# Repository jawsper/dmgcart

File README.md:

# dmgcart
DMGcart: STM32F429 based Game Boy flashcart

These are the hardware design files for the DMGcart.

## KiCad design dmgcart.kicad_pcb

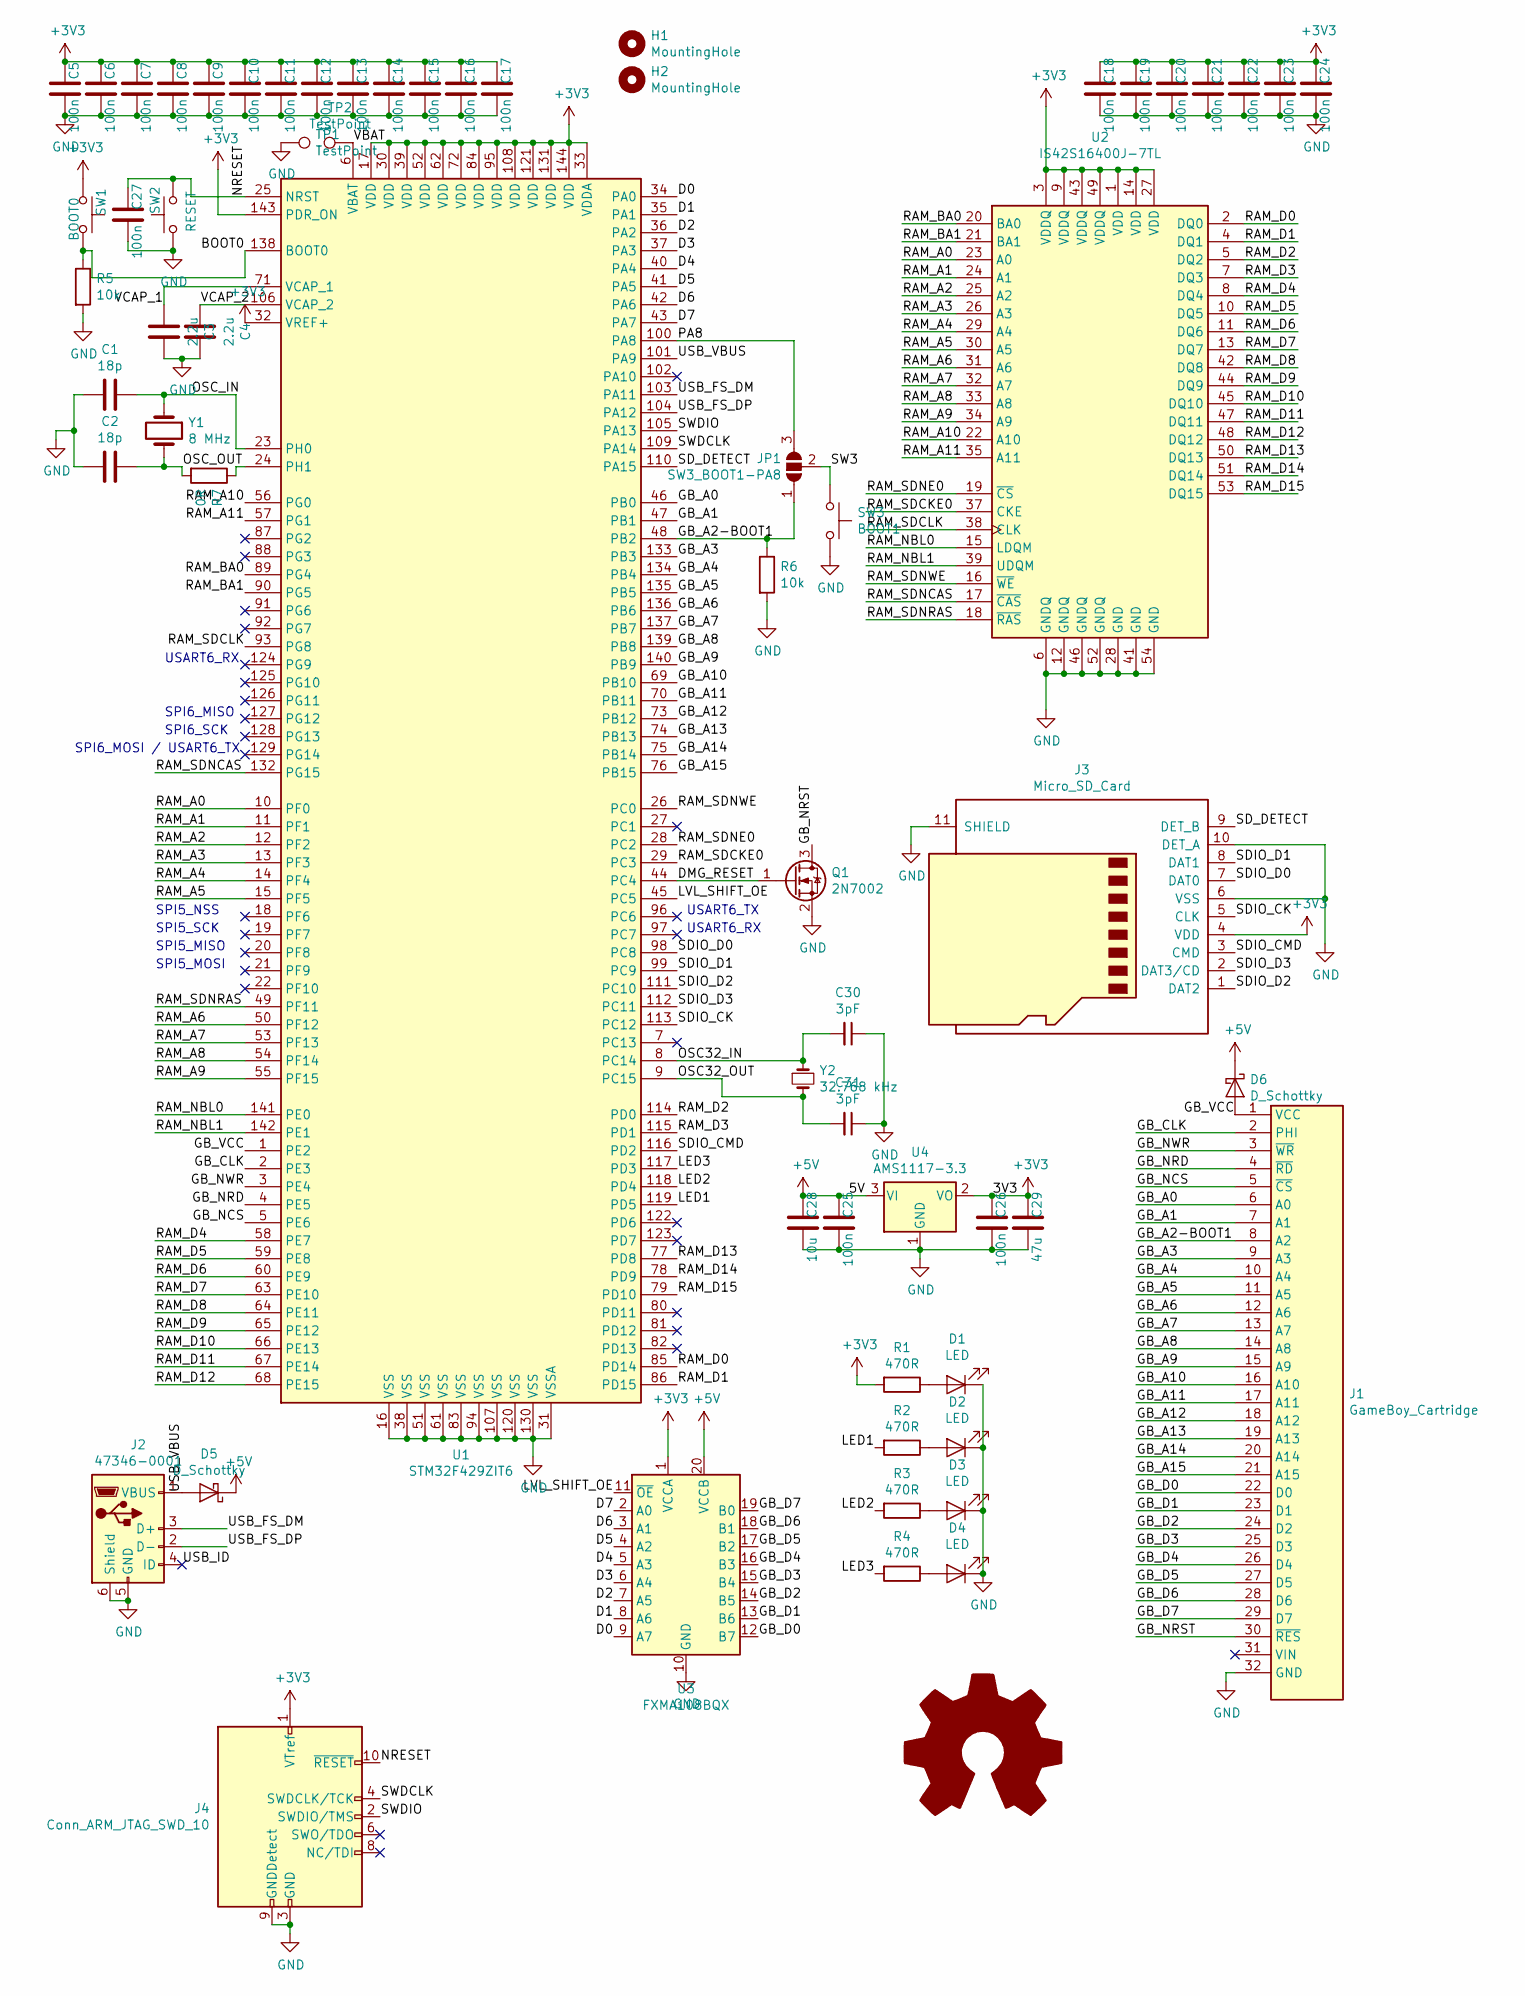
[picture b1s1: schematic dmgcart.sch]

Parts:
C1, C2: 18p; C_0603_1608Metric; Mouser 80-C0603C180K5RACTU
C3, C4: 2.2u; C_0603_1608Metric; Mouser 963-UMK107BBJ225KA-T
C5, C6, C7, C8, C9, C10, C11, C12, C13, C14, C15, C16, C17, C18, C19, C20, C21, C22, C23, C24, C25, C26, C27: 100n; C_0603_1608Metric; Mouser 80-C0603C104K5REC
C28: 10u; C_0603_1608Metric
C29: 47u; C_0805_2012Metric
C30, C31: 3pF; C_0402_1005Metric
D1, D2, D3, D4: LED; LED_0805_2012Metric
D5, D6: D_Schottky; D_SOD-123
H1: MountingHole; MountingHole_7.2mm
H2: MountingHole; MountingHole_2.3mm
J1: GameBoy_Cartridge; GameBoy_Cartridge_1x32_P1.50mm_Edge
J2: 47346-0001; USB_Micro-B_Molex_47346-0001; Mouser 538-47346-0001
J3: Micro_SD_Card; microSD_HC_Hirose_DM3D-SF; Mouser 798-DM3D-SF
J4: Conn_ARM_JTAG_SWD_10; PinHeader_2x05_P1.27mm_Vertical_SMD
JP1: SW3_BOOT1-PA8; SolderJumper-3_P1.3mm_Open_RoundedPad1.0x1.5mm
Q1: 2N7002; SOT-23
R1, R2, R3, R4: 470R; R_0805_2012Metric
R5, R6: 10k; R_0805_2012Metric
R7: 0R; R_0805_2012Metric
SW1: BOOT0; SW_SPST_CK_RS282G05A3
SW2: RESET; SW_SPST_CK_RS282G05A3
SW3: BOOT1; SW_SPST_CK_RS282G05A3
TP1, TP2: TestPoint; TestPoint_Pad_D1.0mm
U1: STM32F429ZIT6; LQFP-144_20x20mm_P0.5mm; Mouser 511-STM32F429ZIT6
U2: IS42S16400J-7TL; TSOP-II-54_22.2x10.16mm_P0.8mm; Mouser 870-IS42S16400J-7TL
U3: FXMA108BQX; WQFN-20-1EP_2.5x4.5mm_P0.5mm_EP1x2.9mm; Mouser 512-FXMA108BQX
U4: AMS1117-3.3; SOT-223-3_TabPin2
Y1: 8 MHz; Crystal_SMD_0603-2Pin_6.0x3.5mm; Mouser 520-8.0-18-23G-JGNT
Y2: 32.768 kHz; Crystal_SMD_2012-2Pin_2.0x1.2mm; Mouser 815-ABS06W32.768KD2T

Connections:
+3V3: C5.2, C6.2, C7.2, C8.2, C9.2, C10.2, C11.2, C12.2, C13.2, C14.2, C15.2, C16.2, C17.2, C18.2, C19.2, C20.2, C21.2, C22.2, C23.2, C24.2, C26.2, C29.2, J3.4 (VDD), J4.1 (VTref), R1.2, SW1.1, U1.17 (VDD), U1.30 (VDD), U1.32 (VREF+), U1.33 (VDDA), U1.39 (VDD), U1.52 (VDD), U1.62 (VDD), U1.72 (VDD), U1.84 (VDD), U1.95 (VDD), U1.108 (VDD), U1.121 (VDD), U1.131 (VDD), U1.143 (PDR_ON), U1.144 (VDD), U2.1 (VDD), U2.3 (VDDQ), U2.9 (VDDQ), U2.14 (VDD), U2.27 (VDD), U2.43 (VDDQ), U2.49 (VDDQ), U3.1 (VCCA), U4.2 (VO)
+5V: C25.2, C28.2, D5.1 (K), D6.1 (K), U3.20 (VCCB), U4.3 (VI)
/BOOT0: R5.1, SW1.2, U1.138 (BOOT0)
/D0: U1.34 (PA0), U3.9 (A7)
/D1: U1.35 (PA1), U3.8 (A6)
/D2: U1.36 (PA2), U3.7 (A5)
/D3: U1.37 (PA3), U3.6 (A4)
/D4: U1.40 (PA4), U3.5 (A3)
/D5: U1.41 (PA5), U3.4 (A2)
/D6: U1.42 (PA6), U3.3 (A1)
/D7: U1.43 (PA7), U3.2 (A0)
/DMG_RESET: Q1.1 (G), U1.44 (PC4)
/GB_A0: J1.6 (A0), U1.46 (PB0)
/GB_A1: J1.7 (A1), U1.47 (PB1)
/GB_A2-BOOT1: J1.8 (A2), JP1.1 (A), R6.1, U1.48 (PB2)
/GB_A3: J1.9 (A3), U1.133 (PB3)
/GB_A4: J1.10 (A4), U1.134 (PB4)
/GB_A5: J1.11 (A5), U1.135 (PB5)
/GB_A6: J1.12 (A6), U1.136 (PB6)
/GB_A7: J1.13 (A7), U1.137 (PB7)
/GB_A8: J1.14 (A8), U1.139 (PB8)
/GB_A9: J1.15 (A9), U1.140 (PB9)
/GB_A10: J1.16 (A10), U1.69 (PB10)
/GB_A11: J1.17 (A11), U1.70 (PB11)
/GB_A12: J1.18 (A12), U1.73 (PB12)
/GB_A13: J1.19 (A13), U1.74 (PB13)
/GB_A14: J1.20 (A14), U1.75 (PB14)
/GB_A15: J1.21 (A15), U1.76 (PB15)
/GB_CLK: J1.2 (PHI), U1.2 (PE3)
/GB_D0: J1.22 (D0), U3.12 (B7)
/GB_D1: J1.23 (D1), U3.13 (B6)
/GB_D2: J1.24 (D2), U3.14 (B5)
/GB_D3: J1.25 (D3), U3.15 (B4)
/GB_D4: J1.26 (D4), U3.16 (B3)
/GB_D5: J1.27 (D5), U3.17 (B2)
/GB_D6: J1.28 (D6), U3.18 (B1)
/GB_D7: J1.29 (D7), U3.19 (B0)
/GB_NCS: J1.5 (~CS), U1.5 (PE6)
/GB_NRD: J1.4 (~RD), U1.4 (PE5)
/GB_NRST: J1.30 (~RES), Q1.3 (D)
/GB_NWR: J1.3 (~WR), U1.3 (PE4)
/GB_VCC: D6.2 (A), J1.1 (VCC), U1.1 (PE2)
/LED1: R2.2, U1.119 (PD5)
/LED2: R3.2, U1.118 (PD4)
/LED3: R4.2, U1.117 (PD3)
/LVL_SHIFT_OE: U1.45 (PC5), U3.11 (~OE)
/NRESET: C27.2, J4.10 (~RESET~), SW2.2, U1.25 (NRST)
/OSC32_IN: C30.2, U1.8 (PC14), Y2.1
/OSC32_OUT: C31.2, U1.9 (PC15), Y2.2
/OSC_IN: C1.1, U1.23 (PH0), Y1.1
/OSC_OUT: C2.1, R7.2, Y1.2
/PA8: JP1.3 (B), U1.100 (PA8)
/RAM_A0: U1.10 (PF0), U2.23 (A0)
/RAM_A1: U1.11 (PF1), U2.24 (A1)
/RAM_A2: U1.12 (PF2), U2.25 (A2)
/RAM_A3: U1.13 (PF3), U2.26 (A3)
/RAM_A4: U1.14 (PF4), U2.29 (A4)
/RAM_A5: U1.15 (PF5), U2.30 (A5)
/RAM_A6: U1.50 (PF12), U2.31 (A6)
/RAM_A7: U1.53 (PF13), U2.32 (A7)
/RAM_A8: U1.54 (PF14), U2.33 (A8)
/RAM_A9: U1.55 (PF15), U2.34 (A9)
/RAM_A10: U1.56 (PG0), U2.22 (A10)
/RAM_A11: U1.57 (PG1), U2.35 (A11)
/RAM_BA0: U1.89 (PG4), U2.20 (BA0)
/RAM_BA1: U1.90 (PG5), U2.21 (BA1)
/RAM_D0: U1.85 (PD14), U2.2 (DQ0)
/RAM_D1: U1.86 (PD15), U2.4 (DQ1)
/RAM_D2: U1.114 (PD0), U2.5 (DQ2)
/RAM_D3: U1.115 (PD1), U2.7 (DQ3)
/RAM_D4: U1.58 (PE7), U2.8 (DQ4)
/RAM_D5: U1.59 (PE8), U2.10 (DQ5)
/RAM_D6: U1.60 (PE9), U2.11 (DQ6)
/RAM_D7: U1.63 (PE10), U2.13 (DQ7)
/RAM_D8: U1.64 (PE11), U2.42 (DQ8)
/RAM_D9: U1.65 (PE12), U2.44 (DQ9)
/RAM_D10: U1.66 (PE13), U2.45 (DQ10)
/RAM_D11: U1.67 (PE14), U2.47 (DQ11)
/RAM_D12: U1.68 (PE15), U2.48 (DQ12)
/RAM_D13: U1.77 (PD8), U2.50 (DQ13)
/RAM_D14: U1.78 (PD9), U2.51 (DQ14)
/RAM_D15: U1.79 (PD10), U2.53 (DQ15)
/RAM_NBL0: U1.141 (PE0), U2.15 (LDQM)
/RAM_NBL1: U1.142 (PE1), U2.39 (UDQM)
/RAM_SDCKE0: U1.29 (PC3), U2.37 (CKE)
/RAM_SDCLK: U1.93 (PG8), U2.38 (CLK)
/RAM_SDNCAS: U1.132 (PG15), U2.17 (~CAS)
/RAM_SDNE0: U1.28 (PC2), U2.19 (~CS)
/RAM_SDNRAS: U1.49 (PF11), U2.18 (~RAS)
/RAM_SDNWE: U1.26 (PC0), U2.16 (~WE)
/SDIO_CK: J3.5 (CLK), U1.113 (PC12)
/SDIO_CMD: J3.3 (CMD), U1.116 (PD2)
/SDIO_D0: J3.7 (DAT0), U1.98 (PC8)
/SDIO_D1: J3.8 (DAT1), U1.99 (PC9)
/SDIO_D2: J3.1 (DAT2), U1.111 (PC10)
/SDIO_D3: J3.2 (DAT3/CD), U1.112 (PC11)
/SD_DETECT: J3.9 (DET_B), U1.110 (PA15)
/SW3: JP1.2 (C), SW3.1
/SWDCLK: J4.4 (SWDCLK/TCK), U1.109 (PA14)
/SWDIO: J4.2 (SWDIO/TMS), U1.105 (PA13)
/USB_FS_DM: J2.3 (D+), U1.103 (PA11)
/USB_FS_DP: J2.2 (D-), U1.104 (PA12)
/USB_ID: J2.4 (ID)
/USB_VBUS: D5.2 (A), J2.1 (VBUS), U1.101 (PA9)
/VBAT: TP2.1, U1.6 (VBAT)
/VCAP_1: C3.2, U1.71 (VCAP_1)
/VCAP_2: C4.2, U1.106 (VCAP_2)
GND: C1.2, C2.2, C3.1, C4.1, C5.1, C6.1, C7.1, C8.1, C9.1, C10.1, C11.1, C12.1, C13.1, C14.1, C15.1, C16.1, C17.1, C18.1, C19.1, C20.1, C21.1, C22.1, C23.1, C24.1, C25.1, C26.1, C27.1, C28.1, C29.1, C30.1, C31.1, D1.1 (K), D2.1 (K), D3.1 (K), D4.1 (K), J1.32 (GND), J2.5 (GND), J2.6 (Shield), J3.6 (VSS), J3.10 (DET_A), J3.11 (SHIELD), J4.3 (GND), J4.5 (GND), J4.9 (GNDDetect), Q1.2 (S), R5.2, R6.2, SW2.1, SW3.2, TP1.1, U1.16 (VSS), U1.31 (VSSA), U1.38 (VSS), U1.51 (VSS), U1.61 (VSS), U1.83 (VSS), U1.94 (VSS), U1.107 (VSS), U1.120 (VSS), U1.130 (VSS), U2.6 (GNDQ), U2.12 (GNDQ), U2.28 (GND), U2.41 (GND), U2.46 (GNDQ), U2.52 (GNDQ), U2.54 (GND), U3.10 (GND), U4.1 (GND)
unnamed: D1.2 (A), R1.1
unnamed: D2.2 (A), R2.1
unnamed: D3.2 (A), R3.1
unnamed: D4.2 (A), R4.1
unnamed: R7.1, U1.24 (PH1)

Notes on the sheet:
SPI5_NSS
SPI5_SCK
SPI5_MISO
SPI5_MOSI
USART6_RX
SPI6_MISO
SPI6_SCK
SPI6_MOSI / USART6_TX
USART6_TX

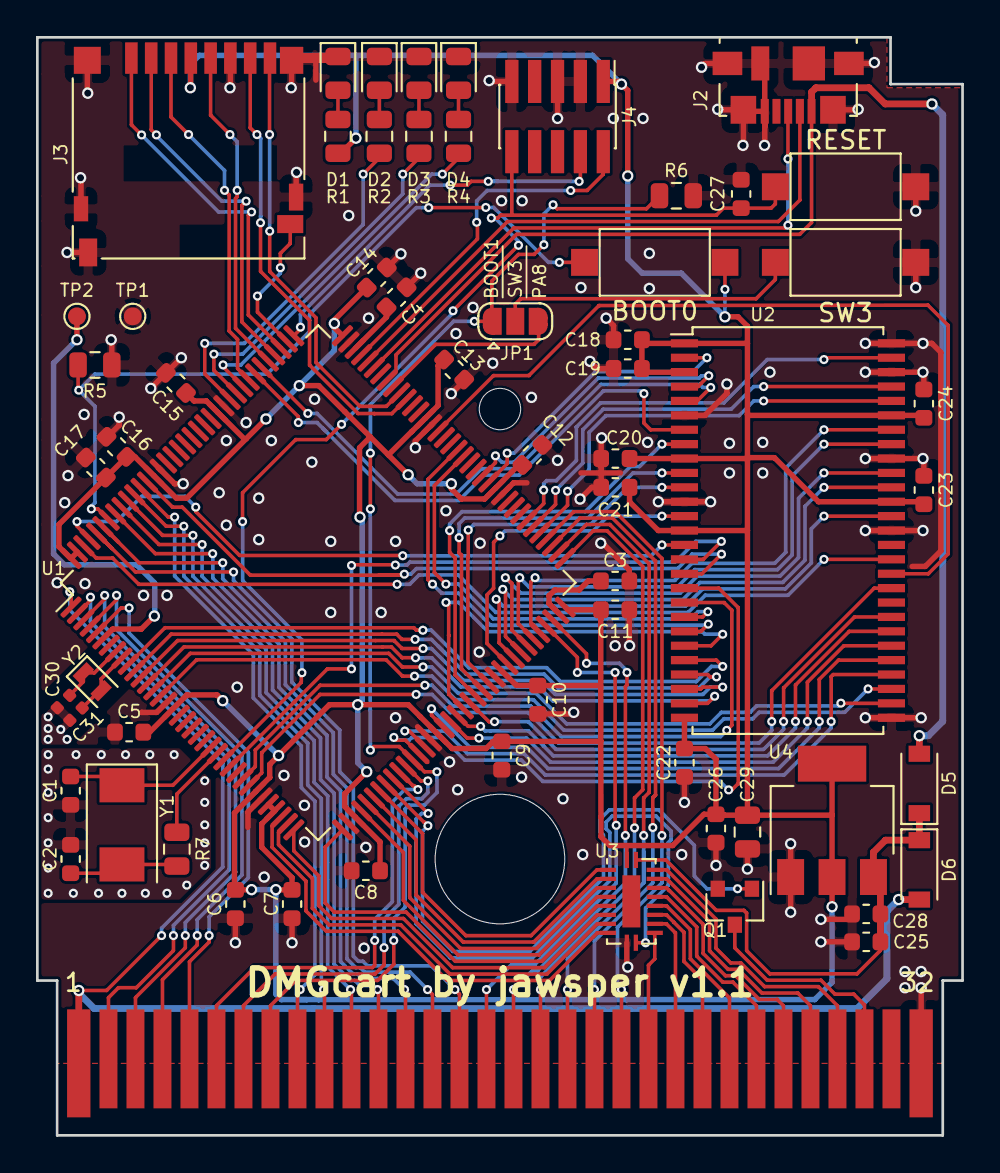
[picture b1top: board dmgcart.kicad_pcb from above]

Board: 2 copper layers, 51.4 x 61.0 mm, 63 parts (0 on the bottom side), 112 nets.

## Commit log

2020-03-06 Initial commit
    Added hardware design files.
    Added external lib with Game Boy footprints.
2020-03-09 Updated design files
    * Moved components up so they shouldn't collide with the case.
    * Rereferenced components so they are sorted by value.
    * Added pad for 32k RTC oscillator.
    * Several small tweaks to routing.
    * Added component value list to back silkscreen.
    * Added board renders
2020-03-10 Added interactive BOM.
    Also added Mouser part no. for the specific 32k xtal that would work.
2020-03-15 Fix #1: Tie /OE of U3 to PC5 instead of VCC.
    This was an error, tying /OE to VCC actually disables the outputs
    of U3. By tying it to a GPIO, it can be controlled by the MCU instead.
    Additional changes:
    * Some small tweaks on the PCB settings in KiCad (board thickness etc)
    * Updated HTML BOM.
    * Changed revision to v1.1
